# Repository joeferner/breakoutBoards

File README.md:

* SI4737-C40-GM - Broadcast AM/FM Radio Receiver

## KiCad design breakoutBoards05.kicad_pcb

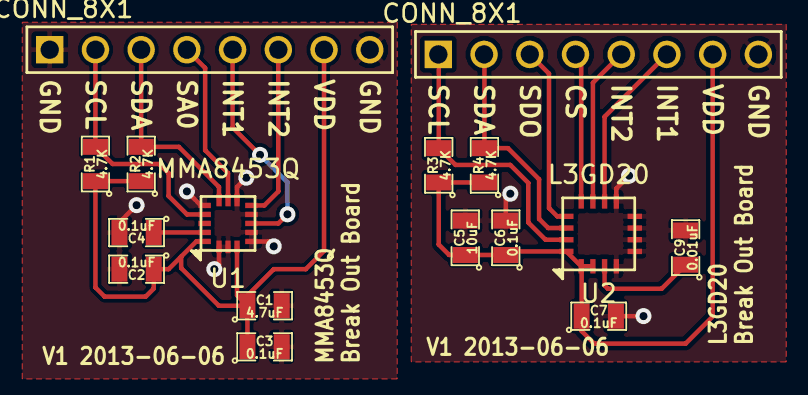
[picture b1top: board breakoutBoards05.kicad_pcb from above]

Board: 2 copper layers, 16 parts (0 on the bottom side), 17 nets.

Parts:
C1: 4.7uF; SM0805
C2, C3, C4, C6, C7: 0.1uF; SM0805
C5: 10uF; SM0805
C9: 0.01uF; SM0805
J1, J2: CONN_8X1; PIN_ARRAY_8X1
R1, R2, R3, R4: 4.7K; SM0805
U1: MMA8453Q; QFN16-0.5-3X3
U2: L3GD20; LGA16-0.65-4X4

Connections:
/ACCBYP: C4.1, U1.2
/ACCGND: C1.2, C2.2, C3.2, C4.2, J1.1, J1.8, U1.5, U1.8, U1.10, U1.12, U1.13, U1.15, U1.16
/ACCINT1: J1.5, U1.11
/ACCINT2: J1.6, U1.9
/ACCSA0: J1.4, U1.7
/ACCSCL: J1.2, R1.2, U1.4
/ACCSDA: J1.3, R2.2, U1.6
/ACCVDD: C1.1, C2.1, C3.1, J1.7, R1.1, R2.1, U1.1, U1.14
/GYROCS: J2.4, U2.5
/GYROGND: C5.2, C6.2, C7.2, C9.2, J2.8, U2.8, U2.9, U2.10, U2.11, U2.12, U2.13
/GYROINT1: J2.6, U2.7
/GYROINT2: J2.5, U2.6
/GYROSCL: J2.1, R3.2, U2.2
/GYROSDA: J2.2, R4.2, U2.3
/GYROSDO: J2.3, U2.4
/GYROVDD: C5.1, C6.1, C7.1, J2.7, R3.1, R4.1, U2.1, U2.15, U2.16
unnamed: C9.1, U2.14

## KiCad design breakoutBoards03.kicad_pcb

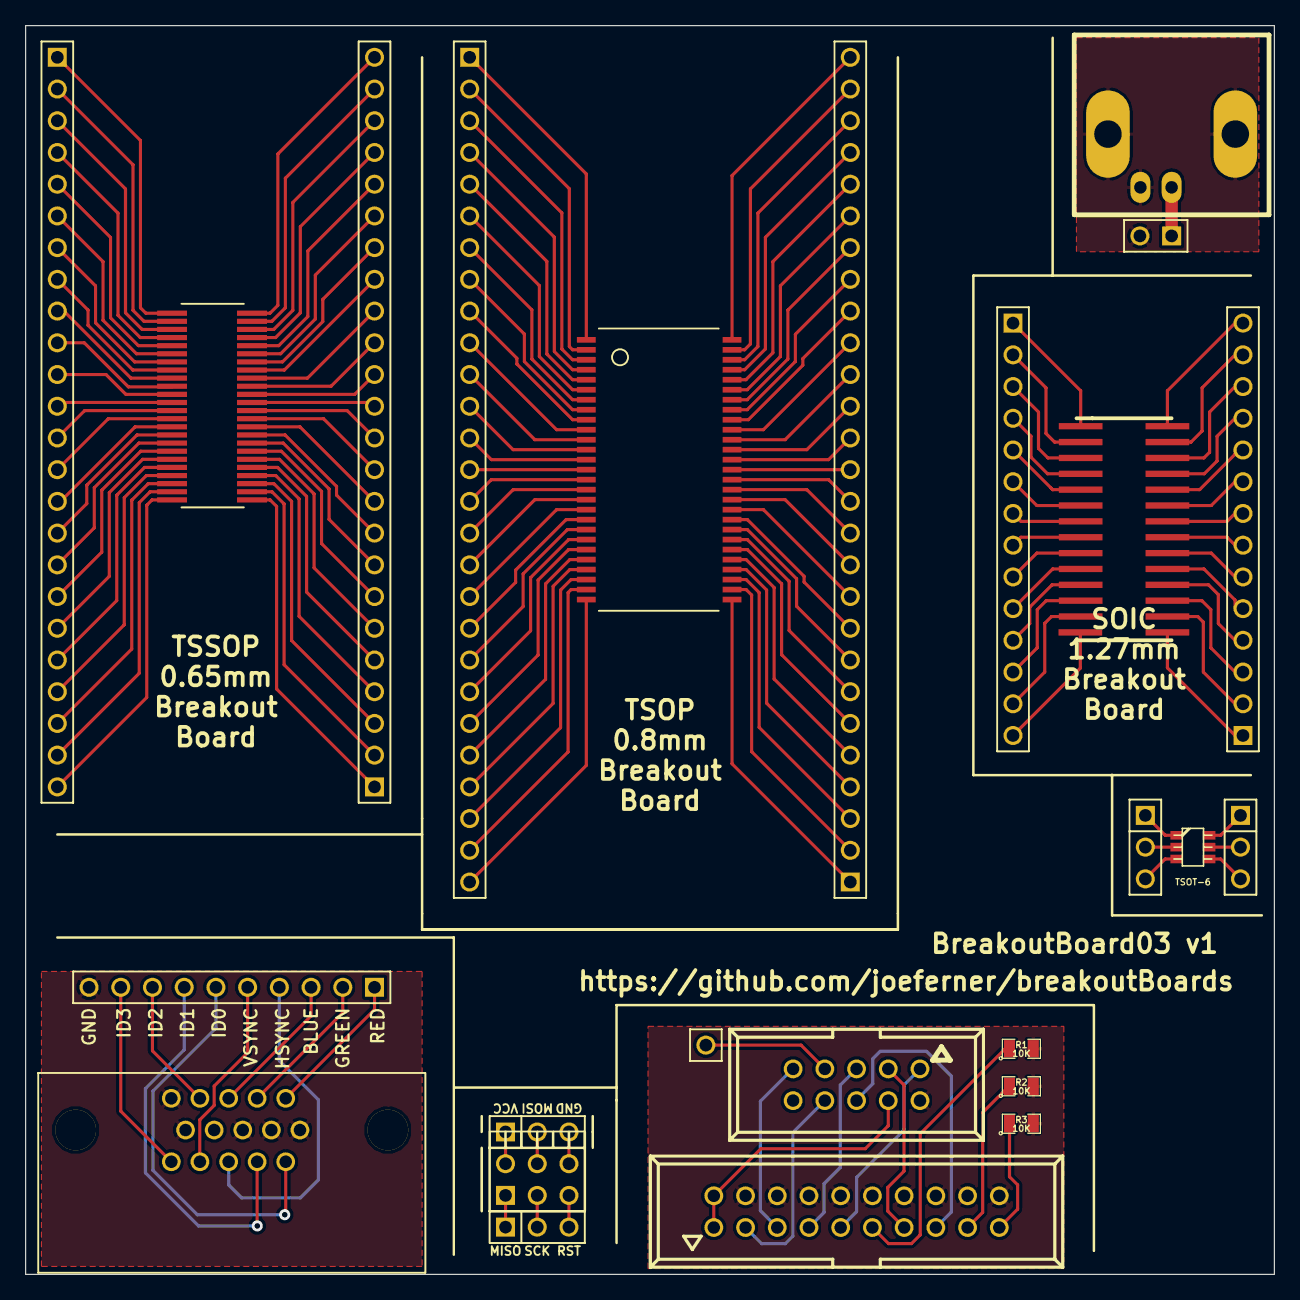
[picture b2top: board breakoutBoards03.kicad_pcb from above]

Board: 2 copper layers, 100.0 x 100.0 mm, 25 parts (0 on the bottom side), 166 nets.

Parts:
J1, J2: CONN_24X1; PIN_ARRAY_24X1
J3: CONN_10X1; PIN_ARRAY_10X1
J4, J5: CONN_27X1; PIN_ARRAY_27X1
J6, J8: CONN_3X1; PIN_ARRAY_3X1
J7: AVRISP; AVR-ICSP-NOOUTLINE
K1, K2: CONN_3; PIN_ARRAY_3X1
P1: CONN_1; PIN_ARRAY_1X1
P2: VGA; VGA_RIGHT_ANGLE
P3: JTAG10; VASCH5x2
P4: JTAG; VASCH10x2
P5: BNC; BNC_Socket_TYCO-AMP_LargePads_RevB_20130411
P6: BNCBREAKOUT; PIN_ARRAY_2X1
P7, P8: CONN_14; PIN_ARRAY_14X1
R1, R2, R3: 10K; SM0805
U1: 48PIN; TSSOP0.65
U2: 54PIN; TSOP54_0.8mm
U3: 28PIN; SO28_BREAKOUT
U4: 6PIN; tsot-6

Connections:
/AVRISPGND: J7.6, J8.3
/AVRISPMISO: J6.1, J7.1
/AVRISPMOSI: J7.4, J8.2
/AVRISPRST: J6.3, J7.5
/AVRISPSCK: J6.2, J7.3
/AVRISPVCC: J7.2, J8.1
/BNCCTR: P5.1, P6.1
/BNCGND: P5.2, P6.2
/JTAGEVTO: P1.1, P3.7
/JTAGGND: P3.2, P4.4, P4.6, P4.8, P4.10, P4.12, P4.14, P4.16, P4.18, P4.20, R1.2, R2.2, R3.2
/JTAGRESET: P3.6, P4.15
/JTAGTCK: P3.1, P4.9
/JTAGTDI: P3.9, P4.5
/JTAGTDO: P3.3, P4.13
/JTAGTMS: P3.5, P4.7
/JTAGTRST: P3.8, P4.3
/JTAGVCC: P3.4, P4.1, P4.2
/VGABLUE: J3.3, P2.3
/VGAGND: J3.10, P2.5, P2.6, P2.7, P2.8, P2.10
/VGAGREEN: J3.2, P2.2
/VGAHSYNC: J3.4, P2.13
/VGAID0: J3.6, P2.11
/VGAID1: J3.7, P2.12
/VGAID2: J3.8, P2.4
/VGAID3: J3.9, P2.15
/VGARED: J3.1, P2.1
/VGAVSYNC: J3.5, P2.14
unnamed: P4.17, R2.1
unnamed: P4.11, R1.1
unnamed: P4.19, R3.1
unnamed: J5.24, U2.51
unnamed: J4.22, U2.22
unnamed: J4.23, U2.23
unnamed: J4.24, U2.24
unnamed: J4.25, U2.25
unnamed: J4.26, U2.26
unnamed: J4.27, U2.27
unnamed: J5.27, U2.54
unnamed: J5.26, U2.53
unnamed: J5.25, U2.52
unnamed: J4.21, U2.21
unnamed: J5.23, U2.50
unnamed: J5.22, U2.49
unnamed: J5.21, U2.48
unnamed: J5.20, U2.47
unnamed: J5.19, U2.46
unnamed: J5.18, U2.45
unnamed: J5.17, U2.44
unnamed: J5.16, U2.43
unnamed: J5.15, U2.42
unnamed: J4.12, U2.12
unnamed: J4.3, U2.3
unnamed: J4.4, U2.4
unnamed: J4.5, U2.5
unnamed: J4.6, U2.6
unnamed: J4.7, U2.7
unnamed: J4.8, U2.8
unnamed: J4.9, U2.9
unnamed: J4.10, U2.10
unnamed: J4.11, U2.11
unnamed: J5.14, U2.41
unnamed: J4.13, U2.13
unnamed: J4.14, U2.14
unnamed: J4.15, U2.15
unnamed: J4.16, U2.16
unnamed: J4.17, U2.17
unnamed: J4.18, U2.18
unnamed: J4.19, U2.19
unnamed: J4.20, U2.20
unnamed: J5.4, U2.31
unnamed: J5.13, U2.40
unnamed: J5.12, U2.39
unnamed: J5.11, U2.38
unnamed: J5.10, U2.37
unnamed: J5.9, U2.36
unnamed: J5.8, U2.35
unnamed: J5.7, U2.34
unnamed: J5.6, U2.33
unnamed: J5.5, U2.32
unnamed: J5.3, U2.30
unnamed: J5.2, U2.29
unnamed: J5.1, U2.28
unnamed: P7.13, U3.13
unnamed: P7.4, U3.4
unnamed: P7.5, U3.5
unnamed: P7.6, U3.6
unnamed: P7.7, U3.7
unnamed: P7.8, U3.8
unnamed: P7.9, U3.9
unnamed: P7.10, U3.10
unnamed: P7.11, U3.11
unnamed: P7.12, U3.12
unnamed: P7.3, U3.3
unnamed: P7.14, U3.14
unnamed: P7.1, U3.1
unnamed: P7.2, U3.2
unnamed: P8.8, U3.22
unnamed: P8.1, U3.15
unnamed: P8.2, U3.16
unnamed: P8.3, U3.17
unnamed: P8.4, U3.18
unnamed: P8.5, U3.19
unnamed: P8.6, U3.20
unnamed: P8.7, U3.21
unnamed: P8.9, U3.23
unnamed: P8.10, U3.24
unnamed: P8.11, U3.25
unnamed: P8.12, U3.26
unnamed: P8.13, U3.27
unnamed: P8.14, U3.28
unnamed: K2.1, U4.6
unnamed: K1.1, U4.1
unnamed: K1.2, U4.2
unnamed: K1.3, U4.3
unnamed: K2.2, U4.5
unnamed: K2.3, U4.4
unnamed: J4.2, U2.2
unnamed: J2.20, U1.44
unnamed: J2.21, U1.45
unnamed: J2.22, U1.46
unnamed: J2.23, U1.47
unnamed: J2.24, U1.48
unnamed: J2.16, U1.40
unnamed: J2.17, U1.41
unnamed: J2.18, U1.42
unnamed: J2.19, U1.43
unnamed: J1.16, U1.16
unnamed: J1.17, U1.17
unnamed: J1.18, U1.18
unnamed: J1.19, U1.19
unnamed: J1.20, U1.20
unnamed: J1.21, U1.21
unnamed: J1.22, U1.22
unnamed: J1.23, U1.23
unnamed: J1.24, U1.24
unnamed: J1.15, U1.15
unnamed: J1.6, U1.6
unnamed: J1.1, U1.1
unnamed: J1.2, U1.2
unnamed: J1.3, U1.3
unnamed: J1.4, U1.4
unnamed: J1.5, U1.5
unnamed: J1.7, U1.7
unnamed: J1.8, U1.8
unnamed: J1.9, U1.9
unnamed: J1.10, U1.10
unnamed: J1.11, U1.11
unnamed: J1.12, U1.12
unnamed: J1.13, U1.13
unnamed: J1.14, U1.14
unnamed: J2.9, U1.33
unnamed: J2.10, U1.34
unnamed: J2.8, U1.32
unnamed: J2.11, U1.35
unnamed: J2.12, U1.36
unnamed: J2.13, U1.37
unnamed: J2.6, U1.30
unnamed: J2.7, U1.31
unnamed: J2.1, U1.25
unnamed: J2.2, U1.26
unnamed: J2.3, U1.27
unnamed: J2.4, U1.28
unnamed: J2.14, U1.38
unnamed: J2.5, U1.29
unnamed: J2.15, U1.39
unnamed: J4.1, U2.1

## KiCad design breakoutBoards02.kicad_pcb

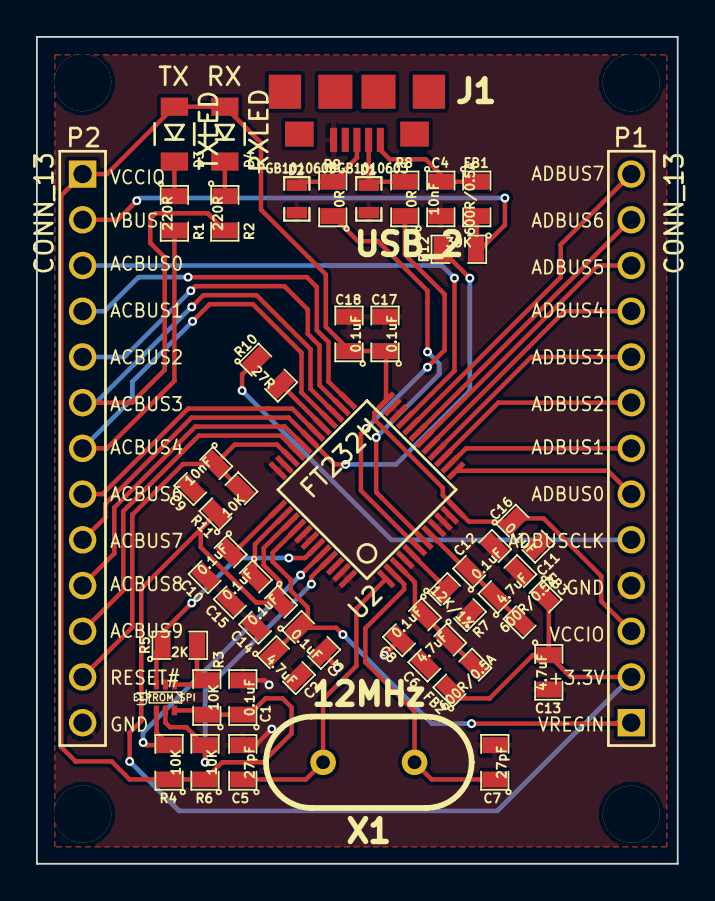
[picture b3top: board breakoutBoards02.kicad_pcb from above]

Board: 2 copper layers, 35.6 x 45.9 mm, 47 parts (0 on the bottom side), 43 nets.

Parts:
C1, C3, C8, C10, C12, C14, C15, C16, C17, C18: 0.1uF; SM0805
C2, C6, C11, C13: 4.7uF; SM0805
C4, C9: 10nF; SM0805
C5, C7: 27pF; SM0805
D1, D2: PGB1010603; SM0603_Resistor
D3: TXLED; LED-1206
D4: RXLED; LED-1206
FB1, FB2, FB3: 600R/0.5A; SM0805
J1: USB_2; USBMICRO
M1, M2, M3, M4: Mounting Hole (0.125"); MOUNTING_HOLE_0.125in
P1, P2: CONN_13; PIN_ARRAY_13X1
R1, R2: 220R; SM0805
R3, R4, R6, R11: 10K; SM0805
R5: 2K; SM0805
R7: 12K/1%; SM0805
R8, R9: 0R; SM0805
R10: 27R; SM0805
R12: 39K; SM0805
U1: EEPROM_SPI; SOT363
U2: FT232H; QFP48
X1: 12MHz; HC-49V

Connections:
+3.3V: C13.1, C14.1, FB2.1, FB3.1, P1.2, R11.1, U2.39
/ACBUS0: P2.3, U2.21
/ACBUS1: P2.4, U2.25
/ACBUS2: P2.5, U2.26
/ACBUS6: P2.8, U2.30
/ACBUS7: P2.9, R12.2, U2.31
/ACBUS8: P2.10, U2.32
/ACBUS9: P2.11, U2.33
/ADBUS0: P1.6, U2.13
/ADBUS1: P1.7, U2.14
/ADBUS2: P1.8, U2.15
/ADBUS3: P1.9, U2.16
/ADBUS4: P1.10, U2.17
/ADBUS5: P1.11, U2.18
/ADBUS6: P1.12, U2.19
/ADBUS7: P1.13, U2.20
/ADBUSCLK: P1.5, R10.1
/RESET#: C9.1, P2.12, R11.2, U2.34
/RXLED#: P2.6, R2.2, U2.27
/TXLED#: P2.7, R1.2, U2.28
/USBDM: R8.1, U2.6
/USBDP: R9.1, U2.7
GND: C1.2, C2.2, C3.2, C4.2, C5.2, C6.2, C7.2, C8.2, C9.2, C10.2, C11.2, C12.2, C13.2, C14.2, C15.2, C16.2, C17.2, C18.2, D1.2, D2.2, J1.5, P1.4, P2.13, R7.2, U1.2, U2.4, U2.9, U2.10, U2.11, U2.22, U2.23, U2.35, U2.36, U2.41, U2.42, U2.47, U2.48
unnamed: R10.2, U2.29
unnamed: D4.2, R2.1
unnamed: D3.2, R1.1
unnamed: C4.1, FB1.1, J1.1
unnamed: D1.1, J1.2, R8.2
unnamed: D2.1, J1.3, R9.2
unnamed: R7.1, U2.5
unnamed: C10.1, U2.37
unnamed: C5.1, U2.1, X1.2
unnamed: C7.1, U2.2, X1.1
unnamed: R6.2, U1.5, U2.45
unnamed: R4.2, U1.4, U2.44
unnamed: R5.1, U1.3, U2.43
unnamed: R3.2, R5.2, U1.1
VBUS: FB1.2, P2.2, R12.1
VCCIO: C1.1, C16.1, C17.1, C18.1, D3.1, D4.1, P1.3, P2.1, R3.1, R4.1, R6.1, U1.6, U2.12, U2.24
VCORE: C15.1, U2.38
VPHY: C6.1, C8.1, FB2.2, U2.3
VPLL: C11.1, C12.1, FB3.2, U2.8
VREGIN: C2.1, C3.1, P1.1, U2.40

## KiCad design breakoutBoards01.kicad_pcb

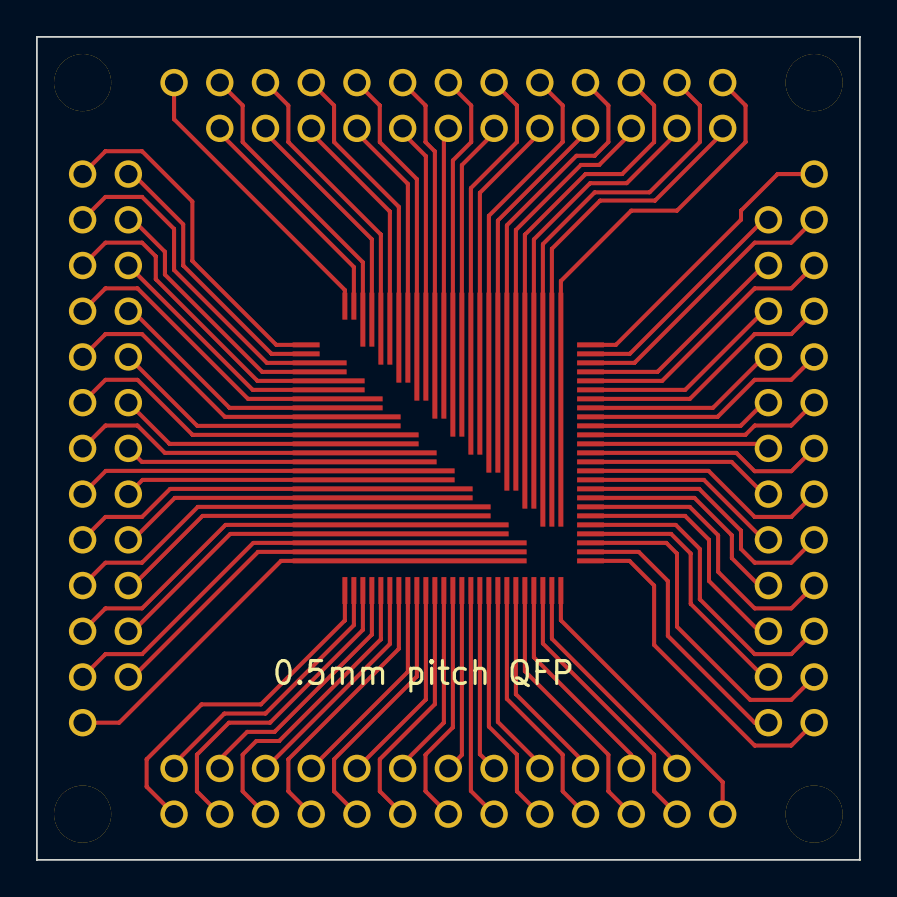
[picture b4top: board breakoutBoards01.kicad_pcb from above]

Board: 2 copper layers, 45.7 x 45.7 mm, 9 parts (0 on the bottom side), 100 nets.

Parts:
J1, J2, J3, J4: CONN_25X1; PIN_ARRAY_12_13
M1, M2, M3, M4: Mounting Hole; MOUNTING_HOLE_0.125in
U1: 100PIN; QFP0.5mm

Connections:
unnamed: J4.16, U1.91
unnamed: J4.20, U1.95
unnamed: J4.21, U1.96
unnamed: J4.22, U1.97
unnamed: J4.23, U1.98
unnamed: J4.24, U1.99
unnamed: J4.25, U1.100
unnamed: J4.19, U1.94
unnamed: J4.18, U1.93
unnamed: J4.17, U1.92
unnamed: J4.15, U1.90
unnamed: J4.14, U1.89
unnamed: J4.13, U1.88
unnamed: J4.12, U1.87
unnamed: J4.10, U1.85
unnamed: J4.1, U1.76
unnamed: J4.2, U1.77
unnamed: J4.3, U1.78
unnamed: J4.4, U1.79
unnamed: J4.5, U1.80
unnamed: J4.6, U1.81
unnamed: J4.7, U1.82
unnamed: J4.8, U1.83
unnamed: J4.9, U1.84
unnamed: J4.11, U1.86
unnamed: J3.10, U1.60
unnamed: J3.24, U1.74
unnamed: J3.14, U1.64
unnamed: J3.23, U1.73
unnamed: J3.13, U1.63
unnamed: J3.22, U1.72
unnamed: J3.12, U1.62
unnamed: J3.21, U1.71
unnamed: J3.11, U1.61
unnamed: J3.20, U1.70
unnamed: J3.15, U1.65
unnamed: J3.9, U1.59
unnamed: J3.8, U1.58
unnamed: J3.7, U1.57
unnamed: J3.6, U1.56
unnamed: J3.5, U1.55
unnamed: J3.4, U1.54
unnamed: J3.3, U1.53
unnamed: J3.2, U1.52
unnamed: J1.1, U1.1
unnamed: J3.19, U1.69
unnamed: J3.18, U1.68
unnamed: J3.17, U1.67
unnamed: J3.16, U1.66
unnamed: J3.25, U1.75
unnamed: J2.22, U1.47
unnamed: J3.1, U1.51
unnamed: J2.25, U1.50
unnamed: J2.24, U1.49
unnamed: J2.23, U1.48
unnamed: J2.21, U1.46
unnamed: J2.20, U1.45
unnamed: J2.19, U1.44
unnamed: J2.18, U1.43
unnamed: J2.17, U1.42
unnamed: J2.16, U1.41
unnamed: J2.15, U1.40
unnamed: J2.14, U1.39
unnamed: J2.13, U1.38
unnamed: J1.10, U1.10
unnamed: J1.19, U1.19
unnamed: J1.18, U1.18
unnamed: J1.17, U1.17
unnamed: J1.16, U1.16
unnamed: J1.15, U1.15
unnamed: J1.14, U1.14
unnamed: J1.13, U1.13
unnamed: J1.12, U1.12
unnamed: J1.11, U1.11
unnamed: J1.20, U1.20
unnamed: J1.9, U1.9
unnamed: J1.8, U1.8
unnamed: J1.7, U1.7
unnamed: J1.6, U1.6
unnamed: J1.5, U1.5
unnamed: J1.4, U1.4
unnamed: J1.3, U1.3
unnamed: J1.2, U1.2
unnamed: J2.4, U1.29
unnamed: J2.12, U1.37
unnamed: J2.11, U1.36
unnamed: J2.10, U1.35
unnamed: J2.9, U1.34
unnamed: J2.8, U1.33
unnamed: J2.7, U1.32
unnamed: J2.6, U1.31
unnamed: J2.5, U1.30
unnamed: J2.3, U1.28
unnamed: J2.2, U1.27
unnamed: J2.1, U1.26
unnamed: J1.25, U1.25
unnamed: J1.24, U1.24
unnamed: J1.23, U1.23
unnamed: J1.22, U1.22
unnamed: J1.21, U1.21

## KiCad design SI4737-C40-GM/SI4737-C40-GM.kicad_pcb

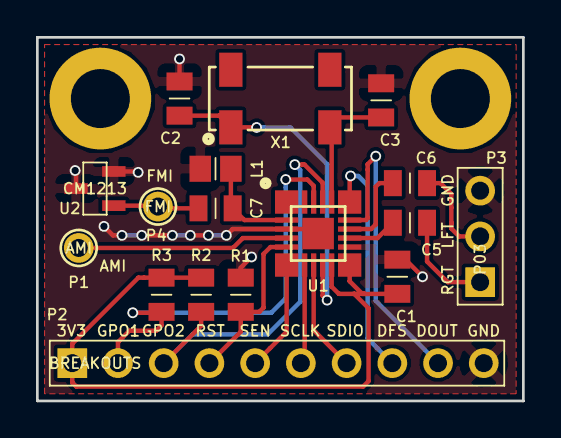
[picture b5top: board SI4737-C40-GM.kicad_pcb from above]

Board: 2 copper layers, 27.0 x 20.2 mm, 19 parts (0 on the bottom side), 19 nets.

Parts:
C1: 0.1uF; CAPC2012X100N
C2, C3: 18pF; CAPC2012X100N
C5, C6: 0.39uF; CAPC2012X100N
C7: 1nF; CAPC2012X100N
L1: 56nH; INDC2012X110N
M1, M2: Mounting Hole; MTGNP565H328Z565P
P1: AMI; HDRV1W66P254_1X1_254X249X838P-ROUND
P2: BREAKOUTS; HDRV10W66P254_1X10_1006X249X838P
P3: P03; HDRV3W66P254_1X3_762X249X838P
P4: FMI; HDRV1W66P254_1X1_254X249X838P-ROUND
R1, R2, R3: 10K; RESC2012X100N
U1: SI4737-C40-GM; QFN50P300X300X60-21N
U2: CM1213; SOT95P237X112_123-3N
X1: 32.768kHz; SOJ550P370X240-4N

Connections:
+3.3V: C1.2, P2.1, R2.1, R3.1, U1.10, U1.11
/AMI: P1.1, U1.4
/DFS: P2.8, U1.16
/DOUT: P2.9, U1.15
/FMI: C7.2, L1.1, U1.2
/GPO1: P2.2, R3.2, U1.19
/GPO2: P2.3, R2.2, U1.18
/LOUT: C6.1, P3.2
/ROUT: C5.1, P3.1
/RST: P2.4, R1.1, U1.5
/SCLK: P2.6, U1.7
/SDIO: P2.7, U1.8
/SEN: P2.5, U1.6
GNDPWR: C1.1, C2.2, C3.2, L1.2, P2.10, P3.3, R1.2, U1.3, U1.12, U1.21, U2.2, U2.3
unnamed: C2.1, U1.9, X1.1
unnamed: C3.1, U1.17, X1.2
unnamed: C5.2, U1.13
unnamed: C6.2, U1.14
unnamed: C7.1, P4.1, U2.1

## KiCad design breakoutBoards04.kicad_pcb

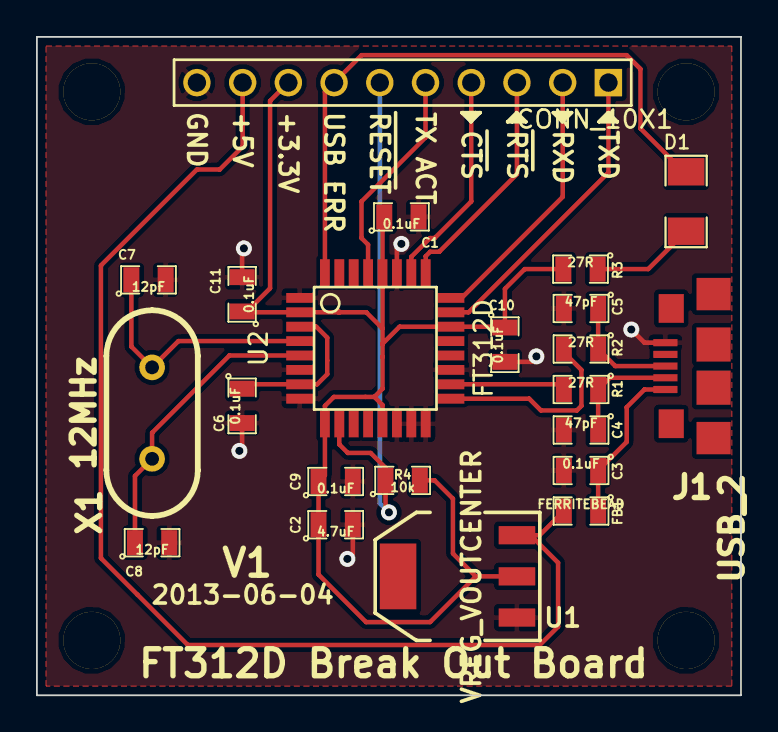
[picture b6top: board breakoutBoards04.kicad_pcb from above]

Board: 2 copper layers, 39.1 x 36.6 mm, 26 parts (0 on the bottom side), 19 nets.

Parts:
C1, C3, C6, C9, C10, C11: 0.1uF; SM0805
C2: 4.7uF; SM0805
C4, C5: 47pF; SM0805
C7, C8: 12pF; SM0805
D1: LED; SM1206
FB1: FERRITEBEAD; SM0805
J1: USB_2; USBMICRO
J2: CONN_10X1; PIN_ARRAY_10X1
M1, M2, M3, M4: Mounting Hole; MOUNTING_HOLE_0.125in
R1, R2, R3: 27R; SM0805
R4: 10k; SM0805
U1: VREG_VOUTCENTER; SOT223
U2: FT312D; QFP32
X1: 12MHz; HC-49V

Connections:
+3.3V: C1.1, C2.1, C9.1, C10.1, C11.1, J2.8, R3.2, R4.2, U1.2, U2.2, U2.9, U2.13, U2.22, U2.28
+5V: FB1.2, J2.9, U1.3
/CTS: J2.4, U2.26
/RESET: J2.6, R4.1, U2.10
/RTS: J2.3, U2.25
/RXD: J2.2, U2.24
/TXD: J2.1, U2.23
/TX_ACTIVE: J2.5, U2.29
/USB_ERROR: D1.2, J2.7, U2.32
GND: C1.2, C2.2, C3.2, C4.2, C5.2, C6.2, C7.2, C8.2, C9.2, C10.2, C11.2, J1.5, J2.10, U1.1, U2.1, U2.6, U2.8, U2.14, U2.15, U2.16, U2.19, U2.27
unnamed: C6.1, U2.3, U2.7
unnamed: D1.1, R3.1
unnamed: C7.1, U2.4, X1.1
unnamed: C8.1, U2.5, X1.2
unnamed: R2.2, U2.17
unnamed: C5.1, J1.3, R2.1
unnamed: C4.1, J1.2, R1.1
unnamed: R1.2, U2.18
unnamed: C3.1, FB1.1, J1.1

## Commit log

2013-04-05 initial
2013-04-05 better layout
2013-04-05 rename
2013-04-05 added readme
2013-04-06 mounting holes and wireup
2013-04-09 new breakout boards
2013-04-09 begin pcb 02
2013-04-09 initial layout
2013-04-10 boards
2013-04-11 TSOP
2013-04-11 soic
2013-04-11 readme
2013-04-11 version numbers
2013-04-17 board 01,02,03 v1
2013-04-26 add mfg part numbers
2013-06-07 accel and gyro
2013-06-09 change footprint
2013-06-10 bob 04 and 05
2013-06-10 added silk
2013-09-03 moved motor controller from telepresenceRobot
2016-05-11 move designs to old
2016-05-26 board layout for SI4737-C40-GM
2016-05-26 SI4737-C40-GM-2016-05-25
